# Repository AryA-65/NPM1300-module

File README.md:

# NPM1300-module (General Doc)
The nPM1300 is a power management IC created and sold by Nordic Semi, intended to be paired with their nRF lineup but can be used by any microcontroller. The nPM1300-module is a 3rd party module that is similar to and based on a reference PCB provided by Nordic Semi. This module allows for simplified testing and cost effective prototyping of a power management IC into a project.

## Board Info (Rev_2)
<table>
  <tr>
    <td>
Current specifications:

- 25.8mm x 25.8mm footprint  
- 7 breakout pins per side  
- Buck converters and LDOs enabled (buck converter voltage is set by placing a resistor on the appropriate Vset pin, check page 47 in the nPM1300 datasheet)  
- Onboard programmable LED
    </td>
    <td>
      <br>
      
  </tr>
</table>

## Updates
Older revisions can be found in "archive" branch:
- Reduced footprint size from 26.5mm x 29.5mm to 25.8mm x 25.8mm
- Added onboard led, and bypass for external led
- Simplified layout, reducing number of total pins
- Added footprints for I2C pullup resistors (short pins for external pullup resistors)
- Flipped board layout
- Reduced GND pin count from 9 to 3

## Schematic
Based off of Nordic's own reference schematic

## Symbol and Footprint
*In progress*

## Software
*Software example code in progress*

## Disclaimer
I OWN NONE OF THE RIGHTS TO THE NPM1300, IT IS A PRODUCT MADE AND SOLD BY NORDIC SEMI. THIS BOARD IS INTENDED TO MAKE INTEGRATION OF THE IC SIMPLER AND HASTLE FREE.

## Documents and Links
List of all documents related to the board:
- [Nordic Semi nPM1300](https://www.nordicsemi.com/Products/nPM1300)
- [nPM1300 reference layouts, production files and BOM](https://www.nordicsemi.com/Products/nPM1300/Downloads#infotabs)
- [Other documentation related to the nPM1300](https://docs.nordicsemi.com/category/npm1300-category)
- [Full nPM1300 datasheet](https://mm.digikey.com/Volume0/opasdata/d220001/medias/docus/6443/NPM1300-QEAA-R.pdf)

## Previous Revisions
- [Rev_1](https://github.com/AryA-65/NPM1300-module/tree/archive)

## License
This project uses the [MIT License](https://github.com/AryA-65/NPM1300-module/blob/main/LICENSE).

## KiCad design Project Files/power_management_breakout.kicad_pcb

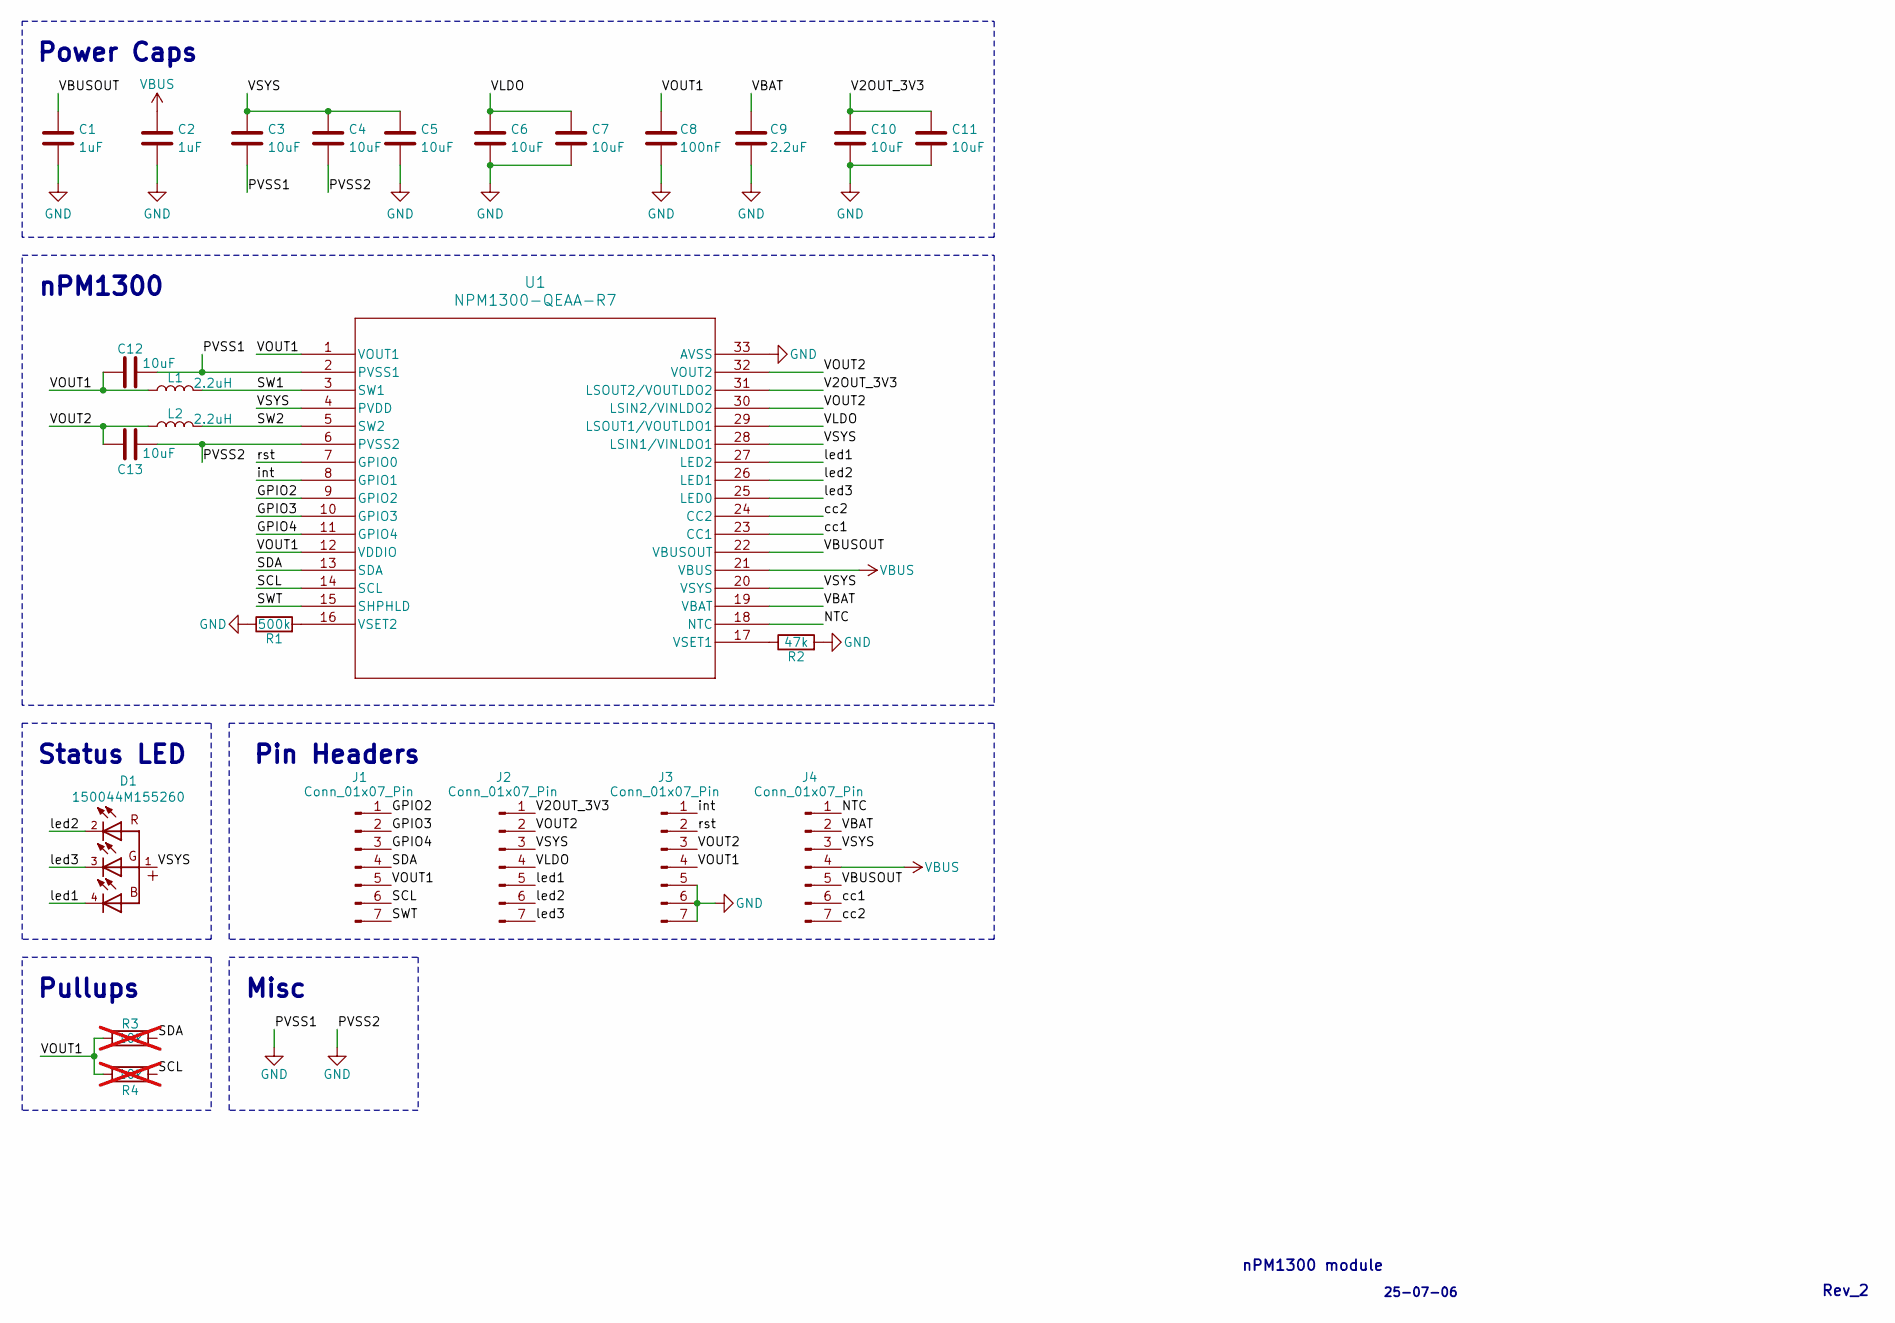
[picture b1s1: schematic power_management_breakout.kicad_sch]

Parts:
C1, C2: 1uF; C_0603_1608Metric
C3, C4, C5, C6, C7, C10, C11, C12, C13: 10uF; C_0603_1608Metric
C8: 100nF; C_0201_0603Metric
C9: 2.2uF; C_0603_1608Metric
D1: 150044M155260
J1, J2, J3, J4: Conn_01x07_Pin; PinHeader_1x07_P2.54mm_Vertical
L1, L2: 2.2uH; INDC2016X100N
R1: 500k; R_0201_0603Metric
R2: 47k; R_0201_0603Metric; LCSC C138139
R3, R4: 10k; R_0201_0603Metric; not fitted
U1: NPM1300-QEAA-R7; QFN32_5X5_NOR

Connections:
/GPIO2: J1.1, U1.9 (GPIO2)
/GPIO3: J1.2, U1.10 (GPIO3)
/GPIO4: J1.3, U1.11 (GPIO4)
/NTC: J4.1, U1.18 (NTC)
/SCL: J1.6, R4.2, U1.14 (SCL)
/SDA: J1.4, R3.2, U1.13 (SDA)
/SW1: L1.2, U1.3 (SW1)
/SW2: L2.2, U1.5 (SW2)
/SWT: J1.7, U1.15 (SHPHLD)
/V2OUT_3V3: C10.1, C11.1, J2.1, U1.31 (LSOUT2/VOUTLDO2)
/VBAT: C9.1, J4.2, U1.19 (VBAT)
/VBUSOUT: C1.1, J4.5, U1.22 (VBUSOUT)
/VLDO: C6.1, C7.1, J2.4, U1.29 (LSOUT1/VOUTLDO1)
/VOUT1: C8.1, C12.1, J1.5, J3.4, L1.1, R3.1, R4.1, U1.1 (VOUT1), U1.12 (VDDIO)
/VOUT2: C13.1, J2.2, J3.3, L2.1, U1.30 (LSIN2/VINLDO2), U1.32 (VOUT2)
/VSYS: C3.1, C4.1, C5.1, D1.1, J2.3, J4.3, U1.4 (PVDD), U1.20 (VSYS), U1.28 (LSIN1/VINLDO1)
/cc1: J4.6, U1.23 (CC1)
/cc2: J4.7, U1.24 (CC2)
/int: J3.1, U1.8 (GPIO1)
/led1: D1.4, J2.5, U1.27 (LED2)
/led2: D1.2, J2.6, U1.26 (LED1)
/led3: D1.3, J2.7, U1.25 (LED0)
/rst: J3.2, U1.7 (GPIO0)
GND: C1.2, C2.2, C3.2, C4.2, C5.2, C6.2, C7.2, C8.2, C9.2, C10.2, C11.2, C12.2, C13.2, J3.5, J3.6, J3.7, R1.1, R2.2, U1.2 (PVSS1), U1.6 (PVSS2), U1.33 (AVSS)
unnamed: R2.1, U1.17 (VSET1)
unnamed: R1.2, U1.16 (VSET2)
VBUS: C2.1, J4.4, U1.21 (VBUS)

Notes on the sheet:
Power Caps
Pin Headers
Pullups
Status LED
25-07-06
nPM1300 module
Misc
Rev_2
nPM1300

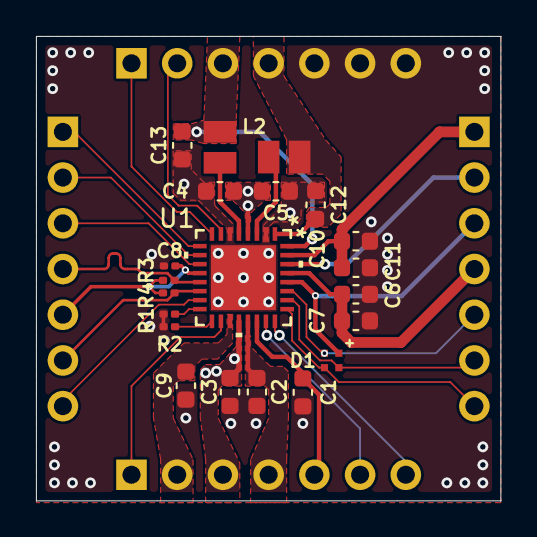
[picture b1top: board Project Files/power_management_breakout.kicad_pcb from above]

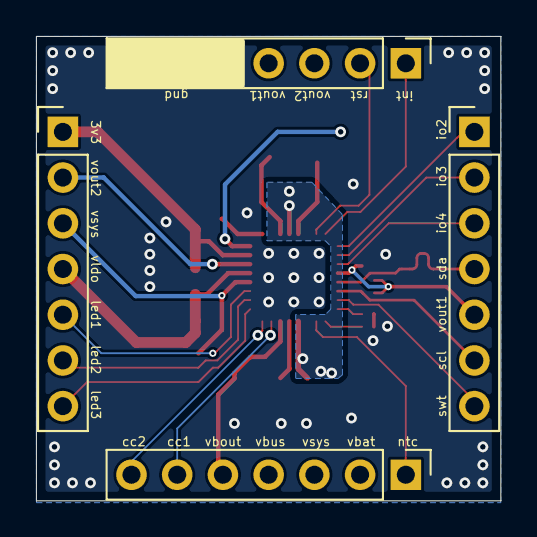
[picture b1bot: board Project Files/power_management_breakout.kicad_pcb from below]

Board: 2 copper layers, 25.8 x 25.8 mm, 25 parts (4 on the bottom side), 27 nets.

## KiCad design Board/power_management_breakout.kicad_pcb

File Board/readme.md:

## Info
This folder includes all files for the board, including the BOM used (different from Nordic BOM), the pick and place files and the project itself, as well as the production files.

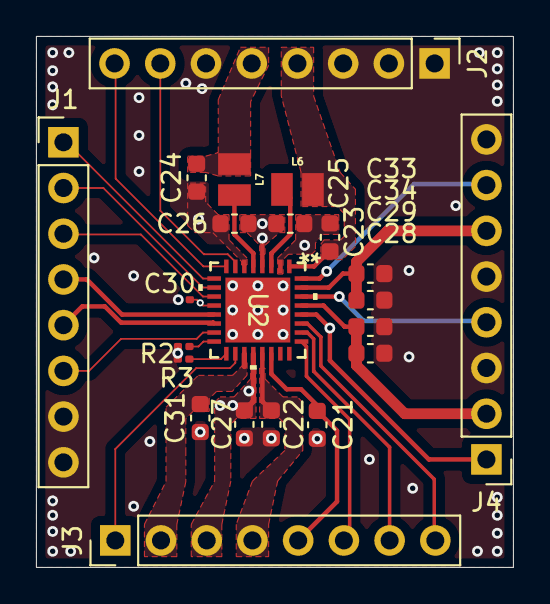
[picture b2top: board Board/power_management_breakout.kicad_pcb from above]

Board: 2 copper layers, 26.5 x 29.5 mm, 22 parts (0 on the bottom side), 22 nets.

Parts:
C21, C22: 1uF; C_0603_1608Metric
C23, C24, C25, C26, C27, C28, C29, C33, C34: 10uF; C_0603_1608Metric
C30: 100nF; C_0201_0603Metric
C31: 2.2uF; C_0603_1608Metric
J1, J2, J3, J4: Conn_01x08_Pin; PinHeader_1x08_P2.54mm_Vertical
L6, L7: 2.2uH; INDC2016X100N
R2: 500k; R_0201_0603Metric
R3: 47k; R_0201_0603Metric
U2: NPM1300-QEAA-R7; QFN32_5X5_NOR

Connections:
/GPIO2: J1.1, U2.9 (GPIO2)
/GPIO3: J1.2, U2.10 (GPIO3)
/GPIO4: J1.3, U2.11 (GPIO4)
/NTC: J3.1, U2.18 (NTC)
/SCL: J1.5, U2.14 (SCL)
/SDA: J1.4, U2.13 (SDA)
/V2OUT_3V3: C33.1, C34.1, J4.6, U2.31 (LSOUT2/VOUTLDO2)
/VBAT: C31.1, J3.2, U2.19 (VBAT)
/VBUSOUT: C21.1, J3.5, U2.22 (VBUSOUT)
/VLDO: C28.1, C29.1, J4.2, U2.29 (LSOUT1/VOUTLDO1)
/VOUT1: C23.1, C30.1, J2.4, L6.1, U2.1 (VOUT1), U2.12 (VDDIO)
/VOUT2: C24.1, J2.5, J4.4, J4.7, L7.1, U2.30 (LSIN2/VINLDO2), U2.32 (VOUT2)
/VSYS: C25.1, C26.1, C27.1, J3.3, J4.1, U2.4 (PVDD), U2.20 (VSYS), U2.28 (LSIN1/VINLDO1)
/int: J2.8, U2.8 (GPIO1)
/led1: J3.8, U2.27 (LED2)
/led2: J3.7, U2.26 (LED1)
/led3: J3.6, U2.25 (LED0)
/rst: J2.7, U2.7 (GPIO0)
GND: C21.2, C22.2, C23.2, C24.2, C25.2, C26.2, C27.2, C28.2, C29.2, C30.2, C31.2, C33.2, C34.2, J1.7, J1.8, J2.1, J2.2, J2.3, J2.6, J4.3, J4.5, J4.8, R2.1, R3.2, U2.2 (PVSS1), U2.6 (PVSS2), U2.33 (AVSS)
unnamed: R3.1, U2.17 (VSET1)
unnamed: R2.2, U2.16 (VSET2)
VBUS: C22.1, J3.4, U2.21 (VBUS)

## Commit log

2025-07-01 Added all project files
2025-07-01 Rename NPM1300-QEAA-R7.pdf to Docs/NPM1300-QEAA-R7.pdf
2025-07-01 Added doc files
2025-07-02 Create 3rd party components
2025-07-02 Create tempo
2025-07-02 Added npm1300 module files
2025-07-02 Added npm1300 files
2025-07-02 Rename tempo.md to PartInfo.md
2025-07-02 Added inductor file
2025-07-07 Cleaned main branch, all previous files in archive
2025-07-07 Create LICENSE
2025-07-07 Rename README.md to Rev_1/README.md
